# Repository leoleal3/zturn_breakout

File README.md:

# zturn_breakout
A custom breakout board for the MYIR Z-Turn single board computer

### v1.0 - Full Breakout Board for Z-Turn
Status: Complete!   
Dimensions: 5.2"x4.5"   
Board Features:  
* 9 2x6 PMOD connectors
* 1 1x6 PMOD connector
* 2mm JTAG connector

### v0.1 - Digilent HS3 JTAG Cable Adapter (2.54mm to 2mm)
Status: Complete!   
This is a simple 2.54mm to 2mm connector adapter to allow the use of the much cheaper [HS3 JTAG cable from Digilent](https://store.digilentinc.com/jtag-hs3-programming-cable/)

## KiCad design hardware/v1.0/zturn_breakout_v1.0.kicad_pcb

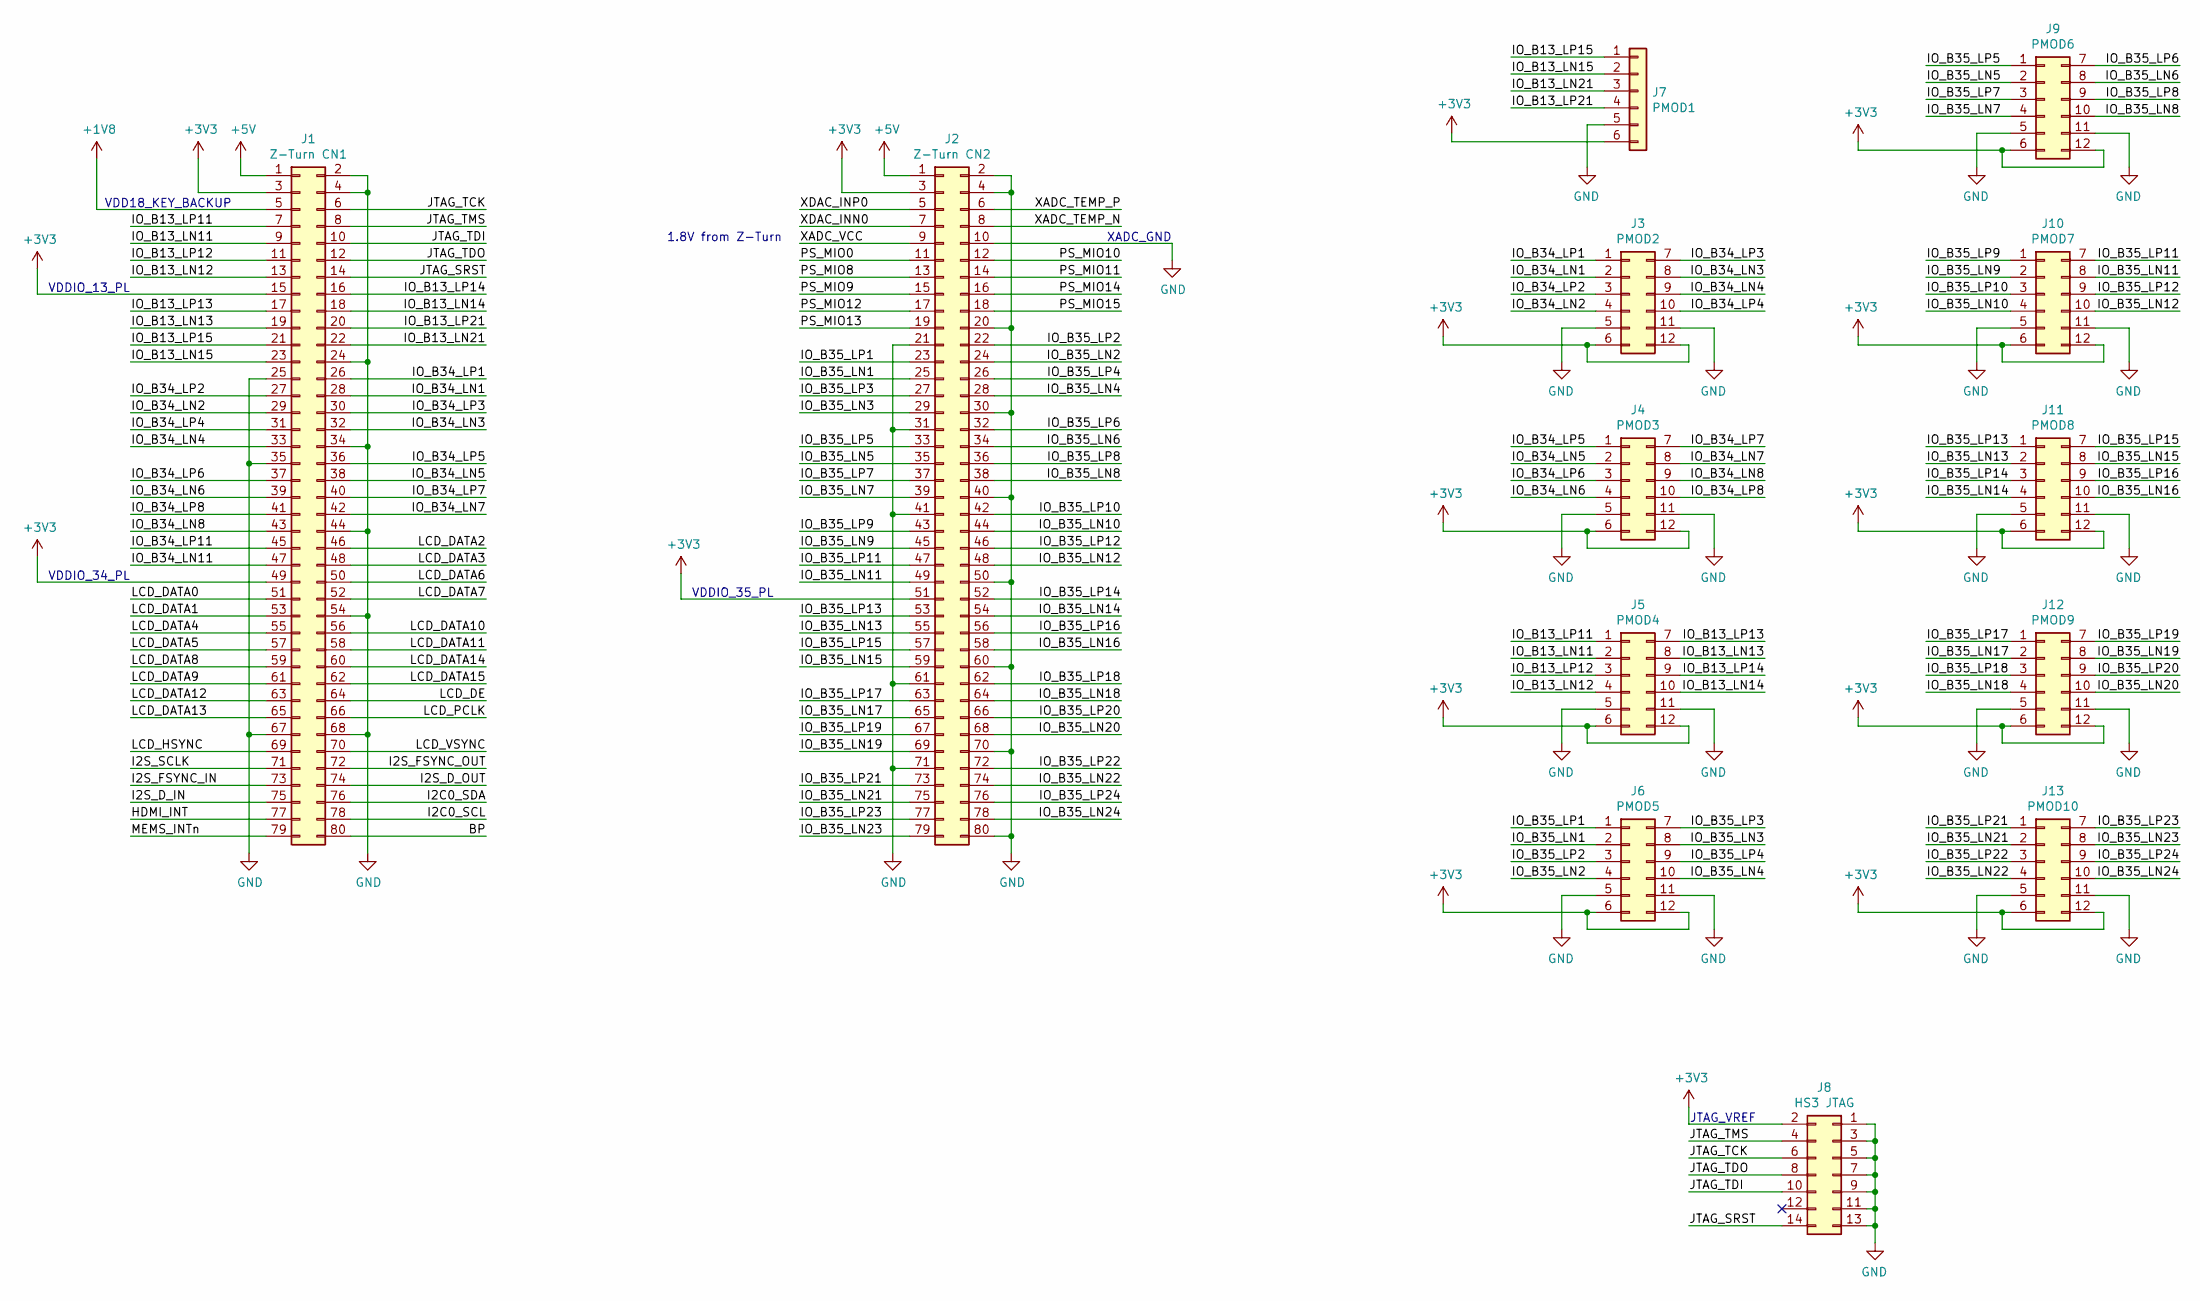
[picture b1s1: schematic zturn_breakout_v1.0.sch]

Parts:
J1: Z-Turn CN1; PinHeader_2x40_P1.27mm_Vertical_SMD; MPN 20021111-00080T4LF
J2: Z-Turn CN2; PinHeader_2x40_P1.27mm_Vertical_SMD; MPN 20021111-00080T4LF
J3: PMOD2; PinSocket_2x06_P2.54mm_Horizontal
J4: PMOD3; PinSocket_2x06_P2.54mm_Horizontal
J5: PMOD4; PinSocket_2x06_P2.54mm_Horizontal
J6: PMOD5; PinSocket_2x06_P2.54mm_Horizontal
J7: PMOD1; PinSocket_1x06_P2.54mm_Horizontal
J8: HS3 JTAG; PinHeader_2x07_P2.00mm_Vertical
J9: PMOD6; PinSocket_2x06_P2.54mm_Horizontal
J10: PMOD7; PinSocket_2x06_P2.54mm_Horizontal
J11: PMOD8; PinSocket_2x06_P2.54mm_Horizontal
J12: PMOD9; PinSocket_2x06_P2.54mm_Horizontal
J13: PMOD10; PinSocket_2x06_P2.54mm_Horizontal

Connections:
+1V8: J1.5
+3V3: J1.3, J1.15, J1.49, J2.3, J2.51, J3.6, J3.12, J4.6, J4.12, J5.6, J5.12, J6.6, J6.12, J7.6, J8.2, J9.6, J9.12, J10.6, J10.12, J11.6, J11.12, J12.6, J12.12, J13.6, J13.12
+5V: J1.1, J2.1
/BP: J1.80
/HDMI_INT: J1.77
/I2C0_SCL: J1.78
/I2C0_SDA: J1.76
/I2S_D_IN: J1.75
/I2S_D_OUT: J1.74
/I2S_FSYNC_IN: J1.73
/I2S_FSYNC_OUT: J1.72
/I2S_SCLK: J1.71
/IO_B13_LN11: J1.9, J5.2
/IO_B13_LN12: J1.13, J5.4
/IO_B13_LN13: J1.19, J5.8
/IO_B13_LN14: J1.18, J5.10
/IO_B13_LN15: J1.23, J7.2
/IO_B13_LN21: J1.22, J7.3
/IO_B13_LP11: J1.7, J5.1
/IO_B13_LP12: J1.11, J5.3
/IO_B13_LP13: J1.17, J5.7
/IO_B13_LP14: J1.16, J5.9
/IO_B13_LP15: J1.21, J7.1
/IO_B13_LP21: J1.20, J7.4
/IO_B34_LN1: J1.28, J3.2
/IO_B34_LN2: J1.29, J3.4
/IO_B34_LN3: J1.32, J3.8
/IO_B34_LN4: J1.33, J3.9
/IO_B34_LN5: J1.38, J4.2
/IO_B34_LN6: J1.39, J4.4
/IO_B34_LN7: J1.42, J4.8
/IO_B34_LN8: J1.43, J4.9
/IO_B34_LN11: J1.47
/IO_B34_LP1: J1.26, J3.1
/IO_B34_LP2: J1.27, J3.3
/IO_B34_LP3: J1.30, J3.7
/IO_B34_LP4: J1.31, J3.10
/IO_B34_LP5: J1.36, J4.1
/IO_B34_LP6: J1.37, J4.3
/IO_B34_LP7: J1.40, J4.7
/IO_B34_LP8: J1.41, J4.10
/IO_B34_LP11: J1.45
/IO_B35_LN1: J2.25, J6.2
/IO_B35_LN2: J2.24, J6.4
/IO_B35_LN3: J2.29, J6.8
/IO_B35_LN4: J2.28, J6.10
/IO_B35_LN5: J2.35, J9.2
/IO_B35_LN6: J2.34, J9.8
/IO_B35_LN7: J2.39, J9.4
/IO_B35_LN8: J2.38, J9.10
/IO_B35_LN9: J2.45, J10.2
/IO_B35_LN10: J2.44, J10.4
/IO_B35_LN11: J2.49, J10.8
/IO_B35_LN12: J2.48, J10.10
/IO_B35_LN13: J2.55, J11.2
/IO_B35_LN14: J2.54, J11.4
/IO_B35_LN15: J2.59, J11.8
/IO_B35_LN16: J2.58, J11.10
/IO_B35_LN17: J2.65, J12.2
/IO_B35_LN18: J2.64, J12.4
/IO_B35_LN19: J2.69, J12.8
/IO_B35_LN20: J2.68, J12.10
/IO_B35_LN21: J2.75, J13.2
/IO_B35_LN22: J2.74, J13.4
/IO_B35_LN23: J2.79, J13.8
/IO_B35_LN24: J2.78, J13.10
/IO_B35_LP1: J2.23, J6.1
/IO_B35_LP2: J2.22, J6.3
/IO_B35_LP3: J2.27, J6.7
/IO_B35_LP4: J2.26, J6.9
/IO_B35_LP5: J2.33, J9.1
/IO_B35_LP6: J2.32, J9.7
/IO_B35_LP7: J2.37, J9.3
/IO_B35_LP8: J2.36, J9.9
/IO_B35_LP9: J2.43, J10.1
/IO_B35_LP10: J2.42, J10.3
/IO_B35_LP11: J2.47, J10.7
/IO_B35_LP12: J2.46, J10.9
/IO_B35_LP13: J2.53, J11.1
/IO_B35_LP14: J2.52, J11.3
/IO_B35_LP15: J2.57, J11.7
/IO_B35_LP16: J2.56, J11.9
/IO_B35_LP17: J2.63, J12.1
/IO_B35_LP18: J2.62, J12.3
/IO_B35_LP19: J2.67, J12.7
/IO_B35_LP20: J2.66, J12.9
/IO_B35_LP21: J2.73, J13.1
/IO_B35_LP22: J2.72, J13.3
/IO_B35_LP23: J2.77, J13.7
/IO_B35_LP24: J2.76, J13.9
/JTAG_SRST: J1.14, J8.14
/JTAG_TCK: J1.6, J8.6
/JTAG_TDI: J1.10, J8.10
/JTAG_TDO: J1.12, J8.8
/JTAG_TMS: J1.8, J8.4
/LCD_DATA0: J1.51
/LCD_DATA1: J1.53
/LCD_DATA2: J1.46
/LCD_DATA3: J1.48
/LCD_DATA4: J1.55
/LCD_DATA5: J1.57
/LCD_DATA6: J1.50
/LCD_DATA7: J1.52
/LCD_DATA8: J1.59
/LCD_DATA9: J1.61
/LCD_DATA10: J1.56
/LCD_DATA11: J1.58
/LCD_DATA12: J1.63
/LCD_DATA13: J1.65
/LCD_DATA14: J1.60
/LCD_DATA15: J1.62
/LCD_DE: J1.64
/LCD_HSYNC: J1.69
/LCD_PCLK: J1.66
/LCD_VSYNC: J1.70
/MEMS_INTn: J1.79
/PS_MIO0: J2.11
/PS_MIO8: J2.13
/PS_MIO9: J2.15
/PS_MIO10: J2.12
/PS_MIO11: J2.14
/PS_MIO12: J2.17
/PS_MIO13: J2.19
/PS_MIO14: J2.16
/PS_MIO15: J2.18
/XADC_TEMP_N: J2.8
/XADC_TEMP_P: J2.6
/XADC_VCC: J2.9
/XDAC_INN0: J2.7
/XDAC_INP0: J2.5
GND: J1.2, J1.4, J1.24, J1.25, J1.34, J1.35, J1.44, J1.54, J1.67, J1.68, J2.2, J2.4, J2.10, J2.20, J2.21, J2.30, J2.31, J2.40, J2.41, J2.50, J2.60, J2.61, J2.70, J2.71, J2.80, J3.5, J3.11, J4.5, J4.11, J5.5, J5.11, J6.5, J6.11, J7.5, J8.1, J8.3, J8.5, J8.7, J8.9, J8.11, J8.13, J9.5, J9.11, J10.5, J10.11, J11.5, J11.11, J12.5, J12.11, J13.5, J13.11

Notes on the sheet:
XADC_GND
VDDIO_13_PL
VDDIO_34_PL
VDDIO_35_PL
VDD18_KEY_BACKUP
1.8V from Z-Turn
JTAG_VREF

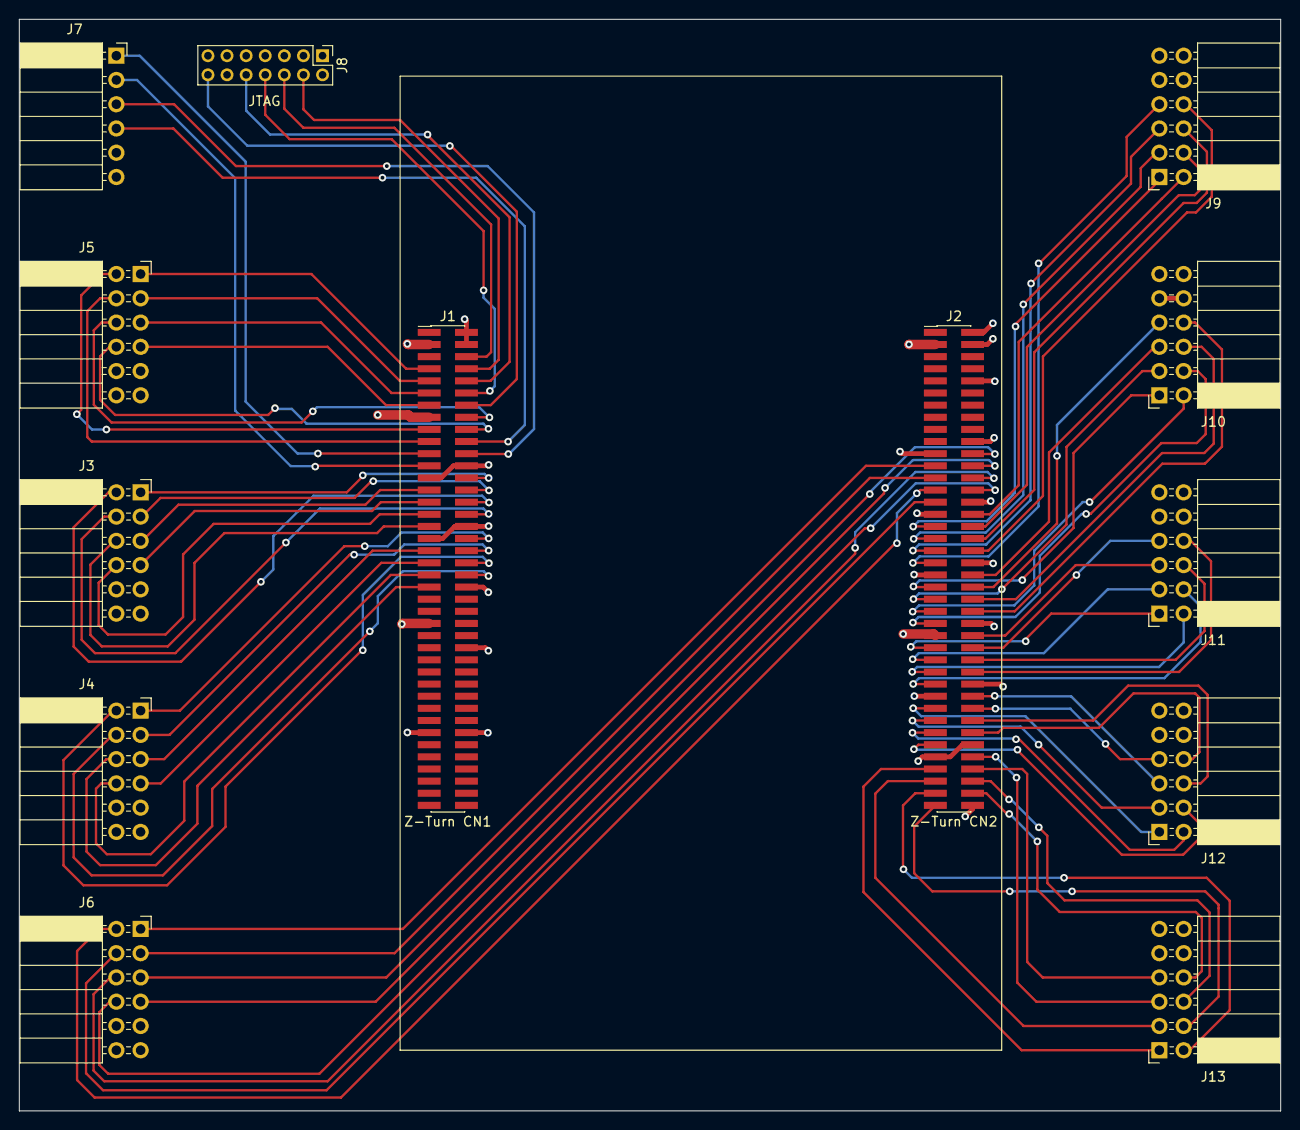
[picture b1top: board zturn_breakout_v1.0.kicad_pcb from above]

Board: 4 copper layers, 132.1 x 114.3 mm, 13 parts (0 on the bottom side), 84 nets.

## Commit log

2019-09-12 Initial commit of v0.1 PCB, HS3 JTAG adapter
2019-09-21 Cleaned up v0.1 and began v1.0 schematic
2019-10-18 Completed schematic and layout of v1.0
2019-10-18 Added board render images
2020-01-11 Added pdf schematic
